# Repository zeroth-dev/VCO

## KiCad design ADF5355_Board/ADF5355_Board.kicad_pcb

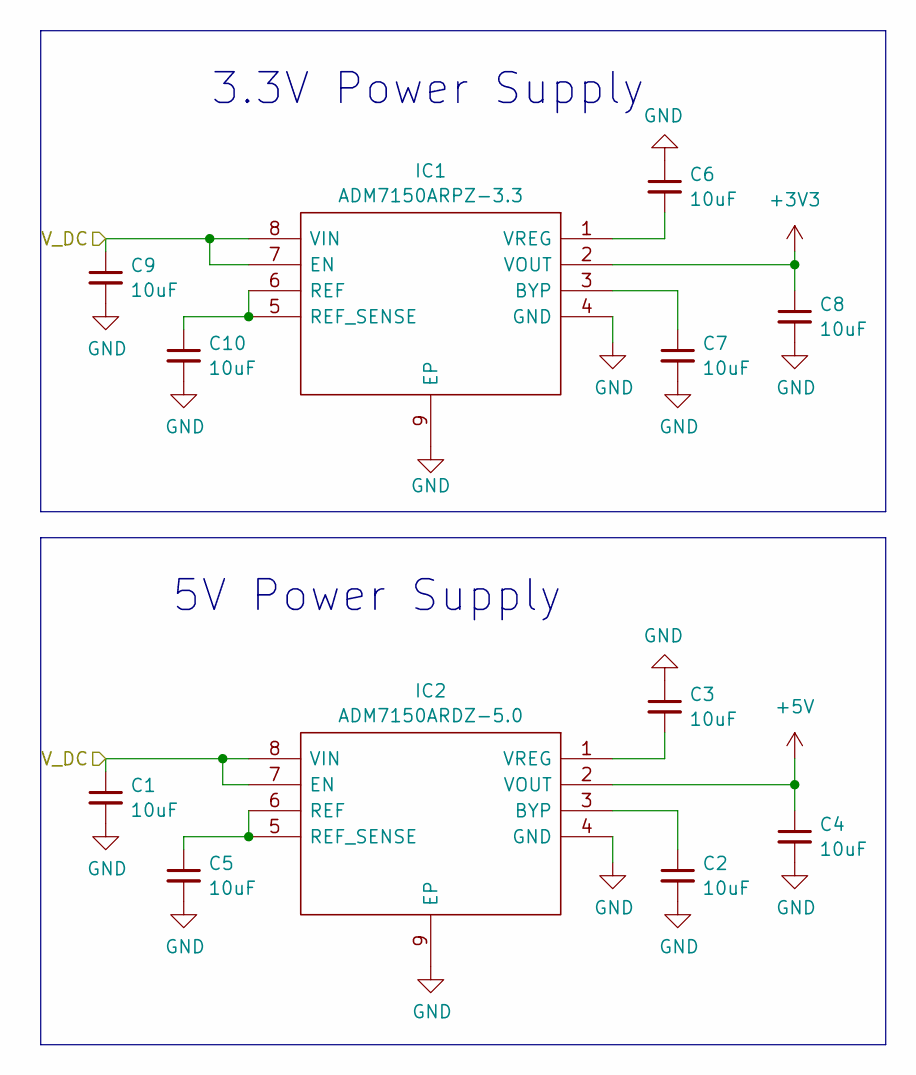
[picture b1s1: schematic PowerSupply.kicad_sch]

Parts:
C1, C2, C3, C4, C5, C6, C7, C8, C9, C10: 10uF; C_0603_1608Metric_Pad1.08x0.95mm_HandSolder
IC1: ADM7150ARPZ-3.3; SOIC-8-1EP_3.9x4.9mm_P1.27mm_EP2.41x3.3mm_ThermalVias; Manufacturer_Part_Number ADM7150ACPZ-3.3-R7; Mouser Part Number 584-ADM7150ACPZ3.3R7
IC2: ADM7150ARDZ-5.0; SOIC-8-1EP_3.9x4.9mm_P1.27mm_EP2.41x3.3mm_ThermalVias; Manufacturer_Part_Number ADM7150ARDZ-5.0; Mouser Part Number 584-ADM7150ARDZ-5.0

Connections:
+3V3: C8.1, IC1.2 (VOUT); also elsewhere on the board
+5V: C4.1, IC2.2 (VOUT); also elsewhere on the board
/Connectors/V_DC: C1.1, C9.1, IC1.7 (EN), IC1.8 (VIN), IC2.7 (EN), IC2.8 (VIN); also elsewhere on the board
GND: C1.2, C2.2, C3.1, C4.2, C5.2, C6.1, C7.2, C8.2, C9.2, C10.2, IC1.4 (GND), IC1.9 (EP), IC2.4 (GND), IC2.9 (EP); also elsewhere on the board
unnamed: C7.1, IC1.3 (BYP)
unnamed: C10.1, IC1.5 (REF_SENSE), IC1.6 (REF)
unnamed: C6.2, IC1.1 (VREG)
unnamed: C2.1, IC2.3 (BYP)
unnamed: C5.1, IC2.5 (REF_SENSE), IC2.6 (REF)
unnamed: C3.2, IC2.1 (VREG)

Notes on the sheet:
3.3V Power Supply
5V Power Supply

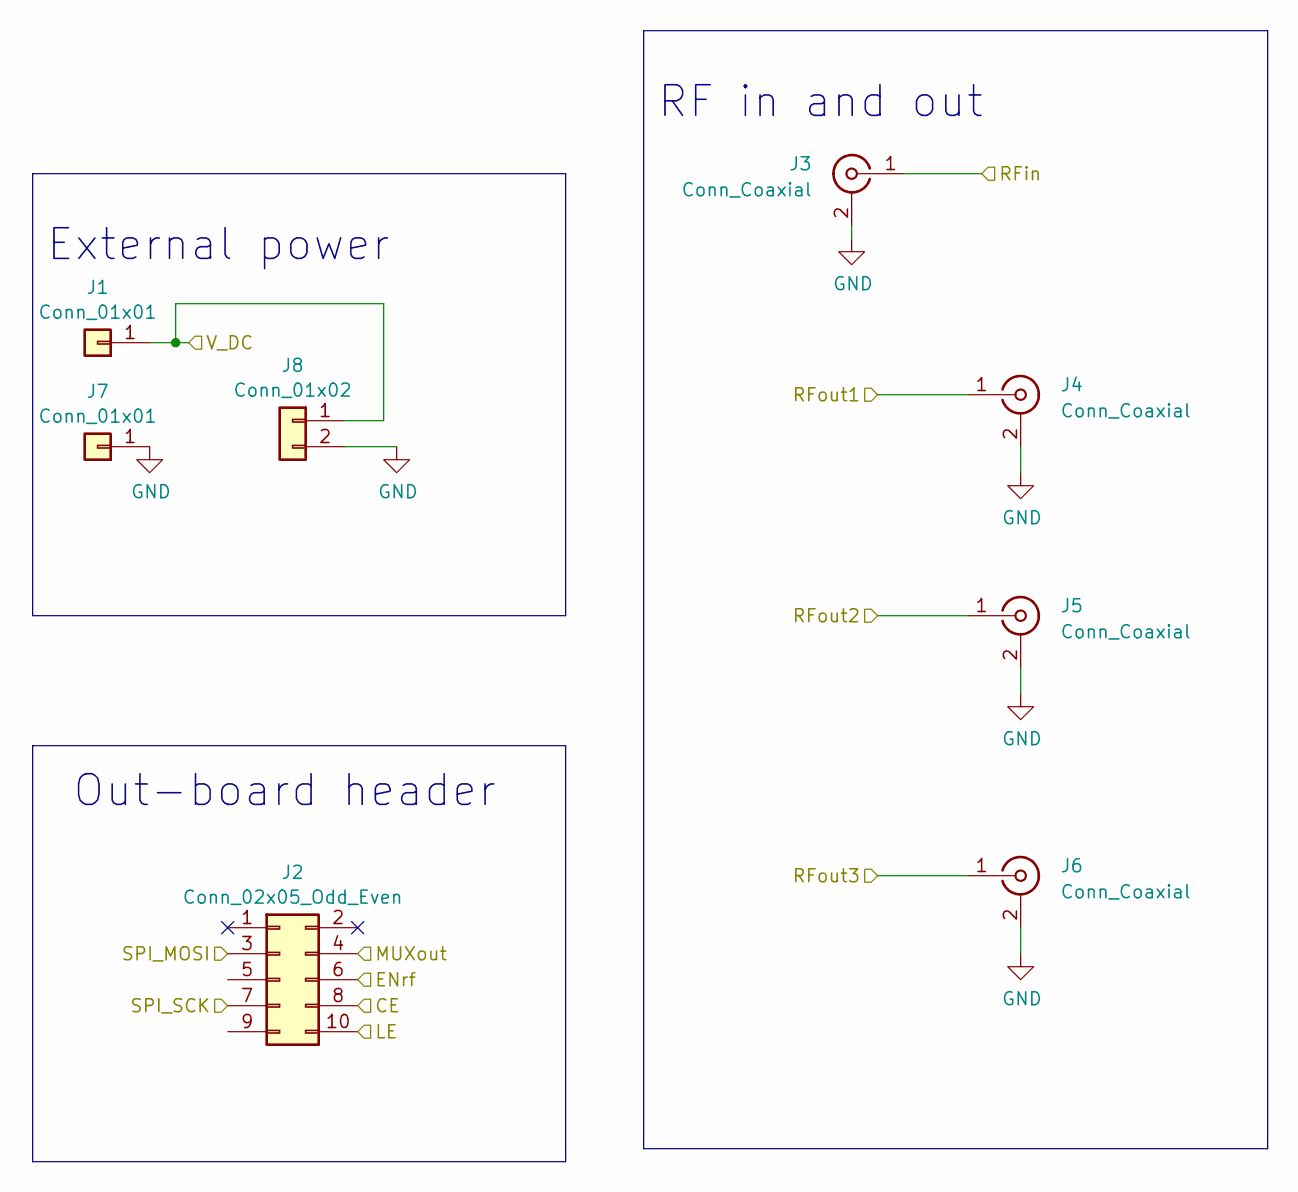
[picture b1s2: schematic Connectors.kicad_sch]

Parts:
J1, J7: Conn_01x01; deltron-571-0500-4mm-90deg-single-socket
J2: Conn_02x05_Odd_Even; PinHeader_2x05_P2.54mm_Vertical
J3, J4, J5, J6: Conn_Coaxial; SMA_Molex_73251-1153_EdgeMount_Horizontal
J8: Conn_01x02; d2269_100-1512192

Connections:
/ADF5355/CE: J2.8; also elsewhere on the board
/ADF5355/CLK: J2.7; also elsewhere on the board
/ADF5355/DATA: J2.3; also elsewhere on the board
/ADF5355/ENrf: J2.6; also elsewhere on the board
/ADF5355/LE: J2.10; also elsewhere on the board
/ADF5355/MUXout: J2.4; also elsewhere on the board
/ADF5355/RFin: J3.1 (In); also elsewhere on the board
/ADF5355/RFout1: J4.1 (In); also elsewhere on the board
/ADF5355/RFout2: J5.1 (In); also elsewhere on the board
/ADF5355/RFout3: J6.1 (In); also elsewhere on the board
/Connectors/SPI_MISO: J2.5
/Connectors/SPI_NSS: J2.9
/Connectors/V_DC: J1.1, J8.1; also elsewhere on the board
GND: J3.2 (Ext), J4.2 (Ext), J5.2 (Ext), J6.2 (Ext), J7.1, J8.2; also elsewhere on the board

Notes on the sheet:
RF in and out
External power
Out-board header

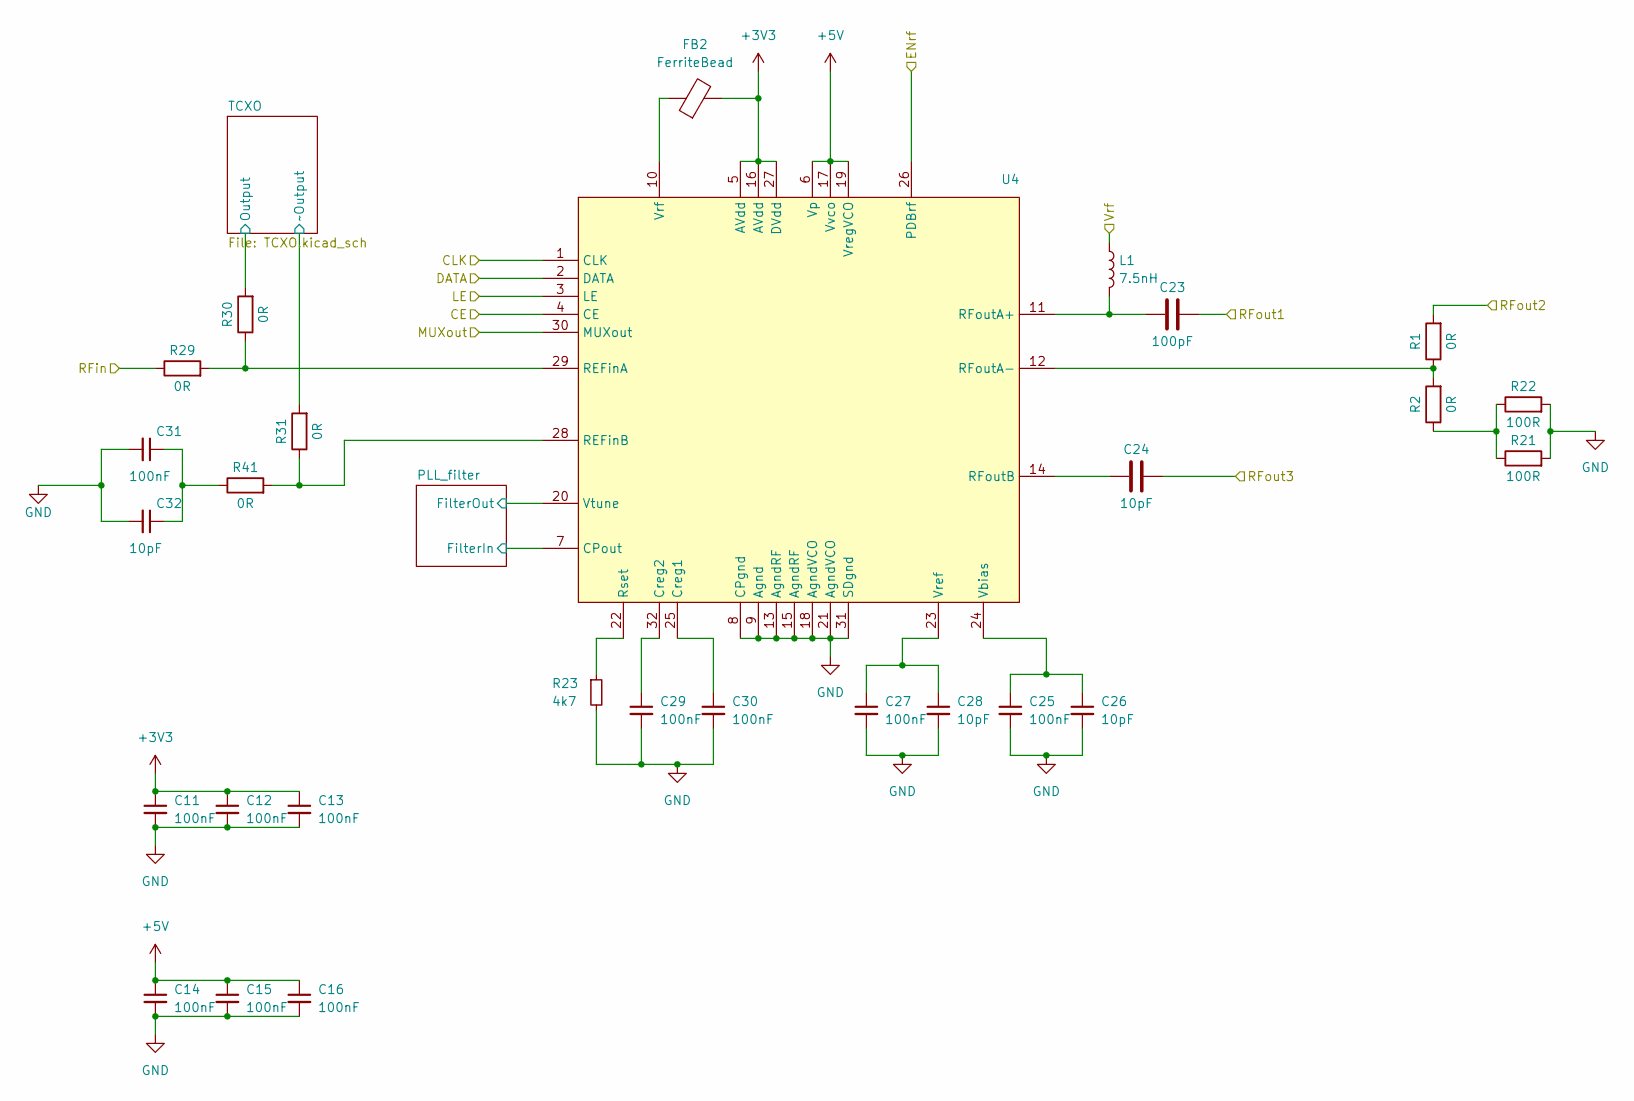
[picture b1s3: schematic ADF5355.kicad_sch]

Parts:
C11, C12, C13, C14, C15, C16, C25, C27, C29, C30, C31: 100nF; C_0402_1005Metric_Pad0.74x0.62mm_HandSolder
C23: 100pF; C_0201_0603Metric_Pad0.64x0.40mm_HandSolder
C24: 10pF; C_0201_0603Metric_Pad0.64x0.40mm_HandSolder
C26, C28, C32: 10pF; C_0402_1005Metric_Pad0.74x0.62mm_HandSolder
FB2: FerriteBead; R_0603_1608Metric_Pad0.98x0.95mm_HandSolder
L1: 7.5nH; C_0402_1005Metric_Pad0.74x0.62mm_HandSolder
R1, R2, R29, R30, R31, R41: 0R; C_0402_1005Metric_Pad0.74x0.62mm_HandSolder
R21, R22: 100R; R_0603_1608Metric_Pad0.98x0.95mm_HandSolder
R23: 4k7; R_0603_1608Metric_Pad0.98x0.95mm_HandSolder
U4: QFN-32_EP_5x5_Pitch0.5mm

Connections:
+3V3: C11.1, C12.1, C13.1, FB2.2, U4.5 (AVdd), U4.16 (AVdd), U4.27 (DVdd); also elsewhere on the board
+5V: C14.1, C15.1, C16.1, U4.6 (Vp), U4.17 (Vvco), U4.19 (VregVCO); also elsewhere on the board
/ADF5355/CE: U4.4 (CE); also elsewhere on the board
/ADF5355/CLK: U4.1 (CLK); also elsewhere on the board
/ADF5355/DATA: U4.2 (DATA); also elsewhere on the board
/ADF5355/ENrf: U4.26 (PDBrf); also elsewhere on the board
/ADF5355/LE: U4.3 (LE); also elsewhere on the board
/ADF5355/MUXout: U4.30 (MUXout); also elsewhere on the board
/ADF5355/PLL_filter/FilterIn: U4.7 (CPout); also elsewhere on the board
/ADF5355/PLL_filter/FilterOut: U4.20 (Vtune); also elsewhere on the board
/ADF5355/RFin: R29.1; also elsewhere on the board
/ADF5355/RFout1: C23.2; also elsewhere on the board
/ADF5355/RFout2: R1.2; also elsewhere on the board
/ADF5355/RFout3: C24.2; also elsewhere on the board
/ADF5355/TCXO/Output: R30.2; also elsewhere on the board
/ADF5355/TCXO/~Output: R31.2; also elsewhere on the board
/ADF5355/Vrf: L1.1
GND: C11.2, C12.2, C13.2, C14.2, C15.2, C16.2, C25.2, C26.2, C27.2, C28.2, C29.2, C30.2, C31.2, C32.2, R21.2, R22.2, R23.2, U4.8 (CPgnd), U4.9 (Agnd), U4.13 (AgndRF), U4.15 (AgndRF), U4.18 (AgndVCO), U4.21 (AgndVCO), U4.31 (SDgnd); also elsewhere on the board
unnamed: C31.1, C32.1, R41.1
unnamed: R2.1, R21.1, R22.1
unnamed: C30.1, U4.25 (Creg1)
unnamed: C29.1, U4.32 (Creg2)
unnamed: R29.2, R30.1, U4.29 (REFinA)
unnamed: R31.1, R41.2, U4.28 (REFinB)
unnamed: C23.1, L1.2, U4.11 (RFoutA+)
unnamed: R1.1, R2.2, U4.12 (RFoutA-)
unnamed: C24.1, U4.14 (RFoutB)
unnamed: R23.1, U4.22 (Rset)
unnamed: C25.1, C26.1, U4.24 (Vbias)
unnamed: C27.1, C28.1, U4.23 (Vref)
unnamed: FB2.1, U4.10 (Vrf)

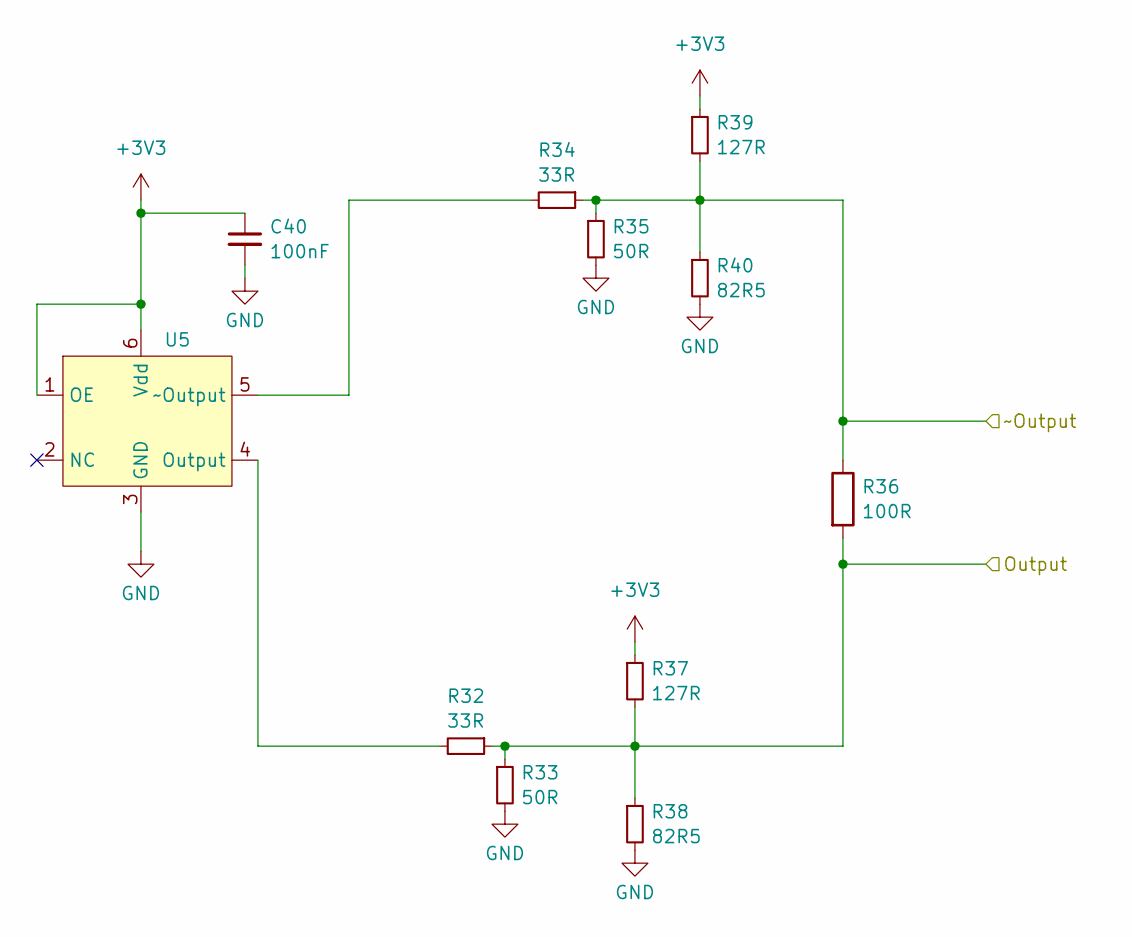
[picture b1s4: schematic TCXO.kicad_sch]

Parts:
C40: 100nF; C_0402_1005Metric_Pad0.74x0.62mm_HandSolder
R32, R34: 33R; C_0402_1005Metric_Pad0.74x0.62mm_HandSolder
R33, R35: 50R; C_0402_1005Metric_Pad0.74x0.62mm_HandSolder
R36: 100R; C_0402_1005Metric_Pad0.74x0.62mm_HandSolder
R37, R39: 127R; C_0402_1005Metric_Pad0.74x0.62mm_HandSolder
R38, R40: 82R5; C_0402_1005Metric_Pad0.74x0.62mm_HandSolder
U5: AX3_XO

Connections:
+3V3: C40.1, R37.1, R39.1, U5.1 (OE), U5.6 (Vdd); also elsewhere on the board
/ADF5355/TCXO/Output: R32.1, R33.1, R36.2, R37.2, R38.1; also elsewhere on the board
/ADF5355/TCXO/~Output: R34.1, R35.1, R36.1, R39.2, R40.1; also elsewhere on the board
GND: C40.2, R33.2, R35.2, R38.2, R40.2, U5.3 (GND); also elsewhere on the board
unnamed: R32.2, U5.4 (Output)
unnamed: R34.2, U5.5 (~Output)

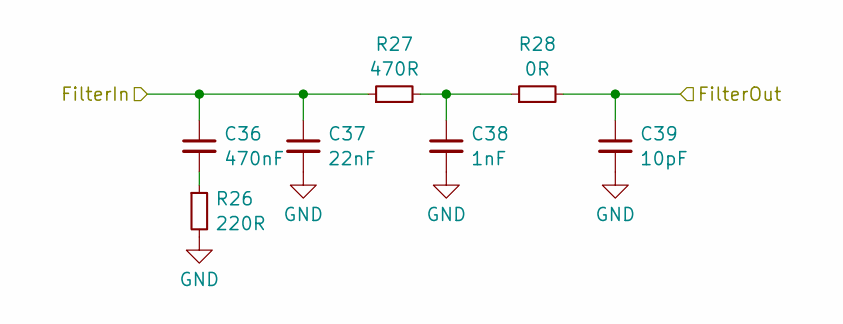
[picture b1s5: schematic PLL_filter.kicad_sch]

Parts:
C36: 470nF; C_0402_1005Metric_Pad0.74x0.62mm_HandSolder
C37: 22nF; C_0402_1005Metric_Pad0.74x0.62mm_HandSolder
C38: 1nF; C_0402_1005Metric_Pad0.74x0.62mm_HandSolder
C39: 10pF; C_0402_1005Metric_Pad0.74x0.62mm_HandSolder
R26: 220R; C_0603_1608Metric_Pad1.08x0.95mm_HandSolder
R27: 470R; C_0603_1608Metric_Pad1.08x0.95mm_HandSolder
R28: 0R; C_0603_1608Metric_Pad1.08x0.95mm_HandSolder

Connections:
/ADF5355/PLL_filter/FilterIn: C36.1, C37.1, R27.1; also elsewhere on the board
/ADF5355/PLL_filter/FilterOut: C39.1, R28.2; also elsewhere on the board
GND: C37.2, C38.2, C39.2, R26.2; also elsewhere on the board
unnamed: C36.2, R26.1
unnamed: C38.1, R27.2, R28.1

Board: 2 copper layers, 66 parts (0 on the bottom side), 41 nets, no tracks yet.

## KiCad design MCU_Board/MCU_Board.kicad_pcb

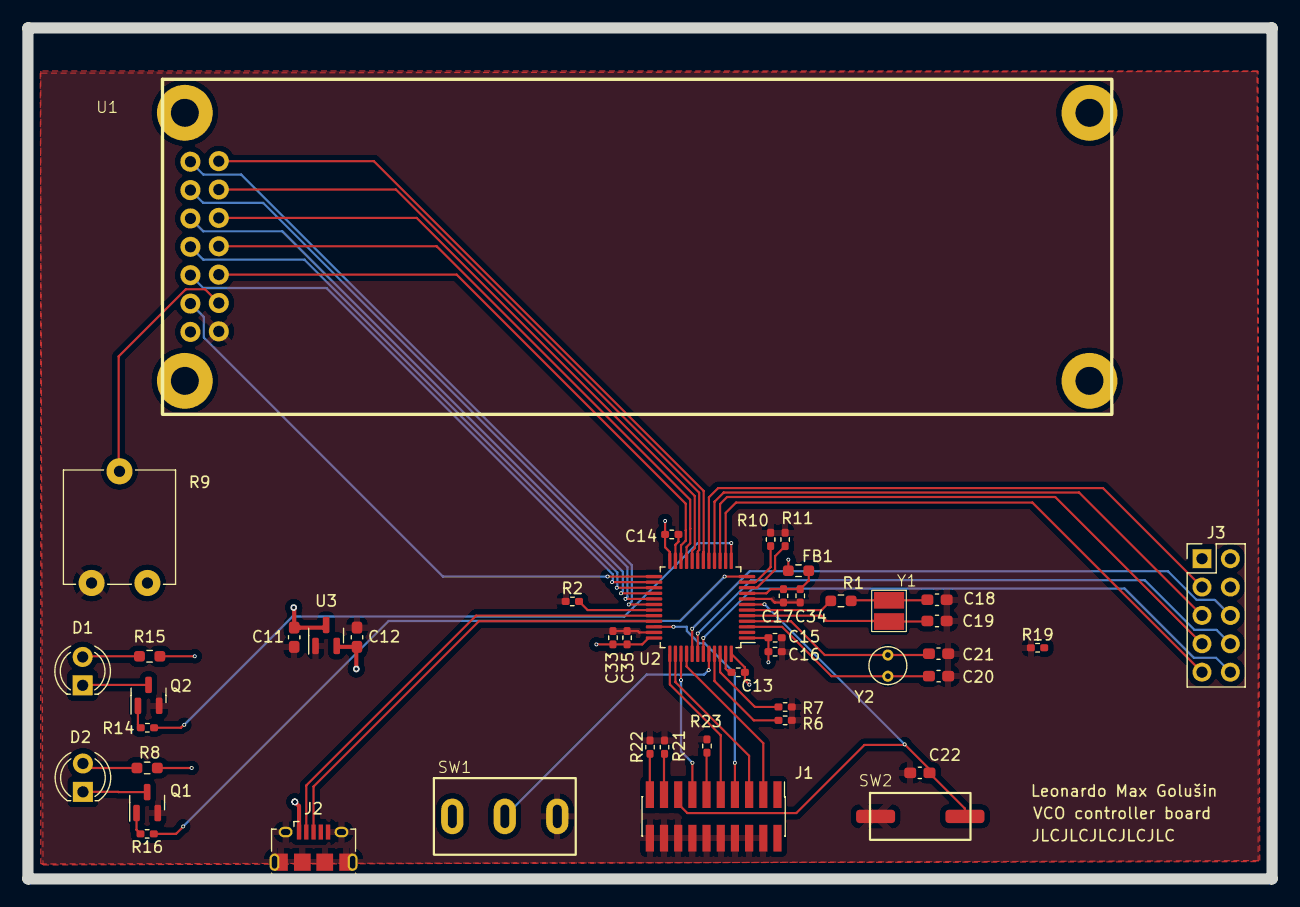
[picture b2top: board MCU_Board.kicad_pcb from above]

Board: 4 copper layers, 111.4 x 76.2 mm, 45 parts (0 on the bottom side), 54 nets.

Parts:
C11, C12: 1uF; C_0603_1608Metric_Pad1.08x0.95mm_HandSolder
C13, C14, C15, C17, C33: 100nF; R_0402_1005Metric_Pad0.72x0.64mm_HandSolder
C16: 10uF; R_0402_1005Metric_Pad0.72x0.64mm_HandSolder
C18, C19: 20pF; C_0603_1608Metric_Pad1.08x0.95mm_HandSolder
C20, C21: 10pF; C_0603_1608Metric_Pad1.08x0.95mm_HandSolder
C22: 100nF; C_0603_1608Metric_Pad1.08x0.95mm_HandSolder
C34, C35: 1uF; R_0402_1005Metric_Pad0.72x0.64mm_HandSolder
D1: Red; LED_D4.0mm
D2: Green; LED_D4.0mm
FB1: FerriteBead; R_0603_1608Metric_Pad0.98x0.95mm_HandSolder
J1: Conn_ARM_JTAG_SWD_20; PinHeader_2x10_P1.27mm_Vertical_SMD
J2: USB_B_Micro; USB_Micro-B_Amphenol_10118194_Horizontal
J3: Conn_02x05_Odd_Even; PinHeader_2x05_P2.54mm_Vertical
Q1, Q2: Q_NMOS_GSD; SOT-23
R1: 390R; R_0603_1608Metric_Pad0.98x0.95mm_HandSolder
R2, R6, R7, R10, R11, R14, R16, R19, R21, R22, R23: 10k; R_0402_1005Metric_Pad0.72x0.64mm_HandSolder
R8: 300R; R_0603_1608Metric_Pad0.98x0.95mm_HandSolder
R9: 10k; Potentiometer_ACP_CA9-V10_Vertical
R15: 200R; R_0603_1608Metric_Pad0.98x0.95mm_HandSolder
SW1: SW_SPDT; Toggle_switch_710X
SW2: SW_Push; WS_TASV_SMT_Switch
U1: 162K-CC_BC-3LP
U2: STM32L433CCTx; LQFP-48_7x7mm_P0.5mm
U3: TPS7A0533PDBZ; SOT-23
Y1: 8MHz; NX3225GD
Y2: 32kHz; Crystal_Round_D3.0mm_Vertical

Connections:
+3V3: C12.1, C13.1, C14.1, C15.1, C16.1, C33.1, C35.1, FB1.1, SW1.1 (A), U2.1 (VBAT), U2.24 (VDD), U2.36 (VDDUSB), U2.48 (VDD), U3.2 (VO)
+5V: C11.1, J2.1 (VBUS), R8.1, R9.1, R15.1, U1.2 (VDD), U3.3 (VI)
/Connectors/CE: J3.8, U2.42 (PB6)
/Connectors/ENrf: J3.6, U2.41 (PB5)
/Connectors/LE: J3.10, U2.43 (PB7)
/Connectors/SPI_MISO: J3.5, U2.16 (PA6)
/Connectors/SPI_MOSI: J3.3, U2.17 (PA7)
/Connectors/SPI_NSS: J3.9, U2.14 (PA4)
/Connectors/SPI_SCK: J3.7, U2.15 (PA5)
/Connectors/TCK: J1.9 (TCK/SWDCLK), U2.37 (PA14)
/Connectors/TDI: J1.5 (TDI), U2.38 (PA15)
/Connectors/TDO: J1.13 (TDO/SWO), U2.39 (PB3)
/Connectors/TMS: J1.7 (TMS/SWDIO), U2.34 (PA13)
/Connectors/TRST: J1.3 (~TRST), U2.40 (PB4)
/MCU/BOOT0_Pin: SW1.2 (B), U2.44 (PH3)
/MCU/OSC32+: C20.2, U2.3 (PC14), Y2.1
/MCU/OSC32-: C21.2, U2.4 (PC15), Y2.2
/MCU/OSC+: C19.2, U2.5 (PH0), Y1.1
/MCU/OSC-: R1.2, U2.6 (PH1)
/MCU/Reset_pin: C22.2, J1.15 (~SRST), SW2.2, U2.7 (NRST)
/MCU/Status_LED_green: R16.1, U2.12 (PA2)
/MCU/Status_LED_red: R14.1, U2.13 (PA3)
/MCU/USB_D+: J2.3 (D+), U2.33 (PA12)
/MCU/USB_D-: J2.2 (D-), U2.32 (PA11)
D0: U1.7 (D0), U2.21 (PB10)
D1: U1.8 (D1), U2.27 (PB14)
D2: U1.9 (D2), U2.20 (PB2)
D3: U1.10 (D3), U2.28 (PB15)
D4: U1.11 (D4), U2.19 (PB1)
D5: U1.12 (D5), U2.29 (PA8)
D6: U1.13 (D6), U2.18 (PB0)
D7: U1.14 (D7), U2.30 (PA9)
EN: U1.6 (E), U2.26 (PB13)
GND: C11.2, C12.2, C13.2, C14.2, C15.2, C16.2, C17.2, C18.1, C19.1, C20.1, C21.1, C22.1, C33.2, C34.2, C35.2, J1.4 (GND), J1.6 (GND), J1.8 (GND), J1.10 (GND), J1.12 (GND), J1.14 (GND), J1.16 (GND), J1.18 (GND), J1.20 (GND), J2.5 (GND), J2.6 (Shield), Q1.2 (S), Q2.2 (S), R2.1, R6.1, R7.1, R9.3, R10.1, R11.1, R19.1, R21.1, R22.2, R23.2, SW1.3 (C), SW2.1, U1.1 (VSS), U2.8 (VSSA), U2.23 (VSS), U2.35 (VSS), U2.47 (VSS), U3.1 (GND)
unnamed: C18.2, R1.1, Y1.2
unnamed: D1.2 (A), R15.2
unnamed: D1.1 (K), Q2.3 (D)
unnamed: D2.2 (A), R8.2
unnamed: D2.1 (K), Q1.3 (D)
unnamed: J1.19 (DBGACK/NC), R22.1
unnamed: J1.17 (DBGRQ/NC), R21.2
unnamed: J1.11 (RTCK), R23.1
unnamed: Q1.1 (G), R16.2
unnamed: Q2.1 (G), R14.2
unnamed: R9.2, U1.3 (VO)
unnamed: R11.2, U2.10 (PA0)
unnamed: R10.2, U2.11 (PA1)
unnamed: R2.2, U2.31 (PA10)
unnamed: R6.2, U2.45 (PB8)
unnamed: R7.2, U2.46 (PB9)
unnamed: R19.2, U2.2 (PC13)
RS: U1.4 (RS), U2.25 (PB12)
R/W: U1.5 (R/W), U2.22 (PB11)
VDDA: C17.1, C34.1, FB1.2, U2.9 (VDDA)

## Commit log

2023-07-17 Moved power ports to the main sheet
2023-07-17 ¸Added USB connector and changed connections
2023-07-27 Finished MCU sheet
2023-07-27 Added LCD screen
    Added LCD 16x2 screen to the project and modified MCU sheet for using aditional GPIO pins for enable and reset pin.
2023-07-29 Added ADF5355 symbol
2023-08-02 Added ADF5355 to the schematic
2023-08-02 Changed the power port
    Changed all power ports to be global instead of them being hierarchical sheet pins
2023-08-03 Added RF connectors
2023-08-06 Added footprints to some components
    Footprints added for:
    SMA connectors
    DC banana connector
    USB connector
    LCD screen
2023-08-08 Added additional footprints and BOM
    Added a bill of materials with most of the components.
    Added footprints for more components
2023-08-08 Updated .gitignore
    Updated .gitignore to ignore excel autosave file
2023-08-08 Changed the status LED circuit
    Changed status LEDs to a BJT driver with 5 V power supply
2023-08-27 Added components for LED subsystem
    Added resistor values and specific resistors and LEDs to BOM for the LED subsystem
    Modified .gitignore to ignore autosave file
2023-09-02 Removed the switch from power supply
    Removed the switch from the main power supply and changed the switch on the boot pin to SDPT switch
2023-09-02 Added PLL filter
    Added components for the PLL filter
    according to the components on evaluation board
    Added specific components to BOM
2023-09-09 Added TCXO and remaining footprints
    Added remaining footprints
    NX3225GD
    710X toggle switch
    SMT button
    Added ClearClock AX3 TCXO symbol and footprint
    Added TCXO schematic with 3 options:
2023-09-10 Split the project in two
    Split the main project in two parts
    One is the MCU part and the second is VCO
    This was made for the purpose of designing two PCB boards.
    In case the MCU part is not designed properly, it can be remade on a cheaper material than the VCO board.
2023-09-11 Added JTAG connector to MCU board
2023-09-12 Added a header for the VCO controls
2023-11-03 Finished MCU board
    Finished MCU board and started finishing up the VCO board
2024-06-29 IDK where I stopped
2025-02-21 Switched to Altium project
2025-03-01 Finished most of the schematic for MCU board
2025-03-04 Added VCO part of the board
    Added VCO base with reference differential input and a basic filter according to the datasheet.
